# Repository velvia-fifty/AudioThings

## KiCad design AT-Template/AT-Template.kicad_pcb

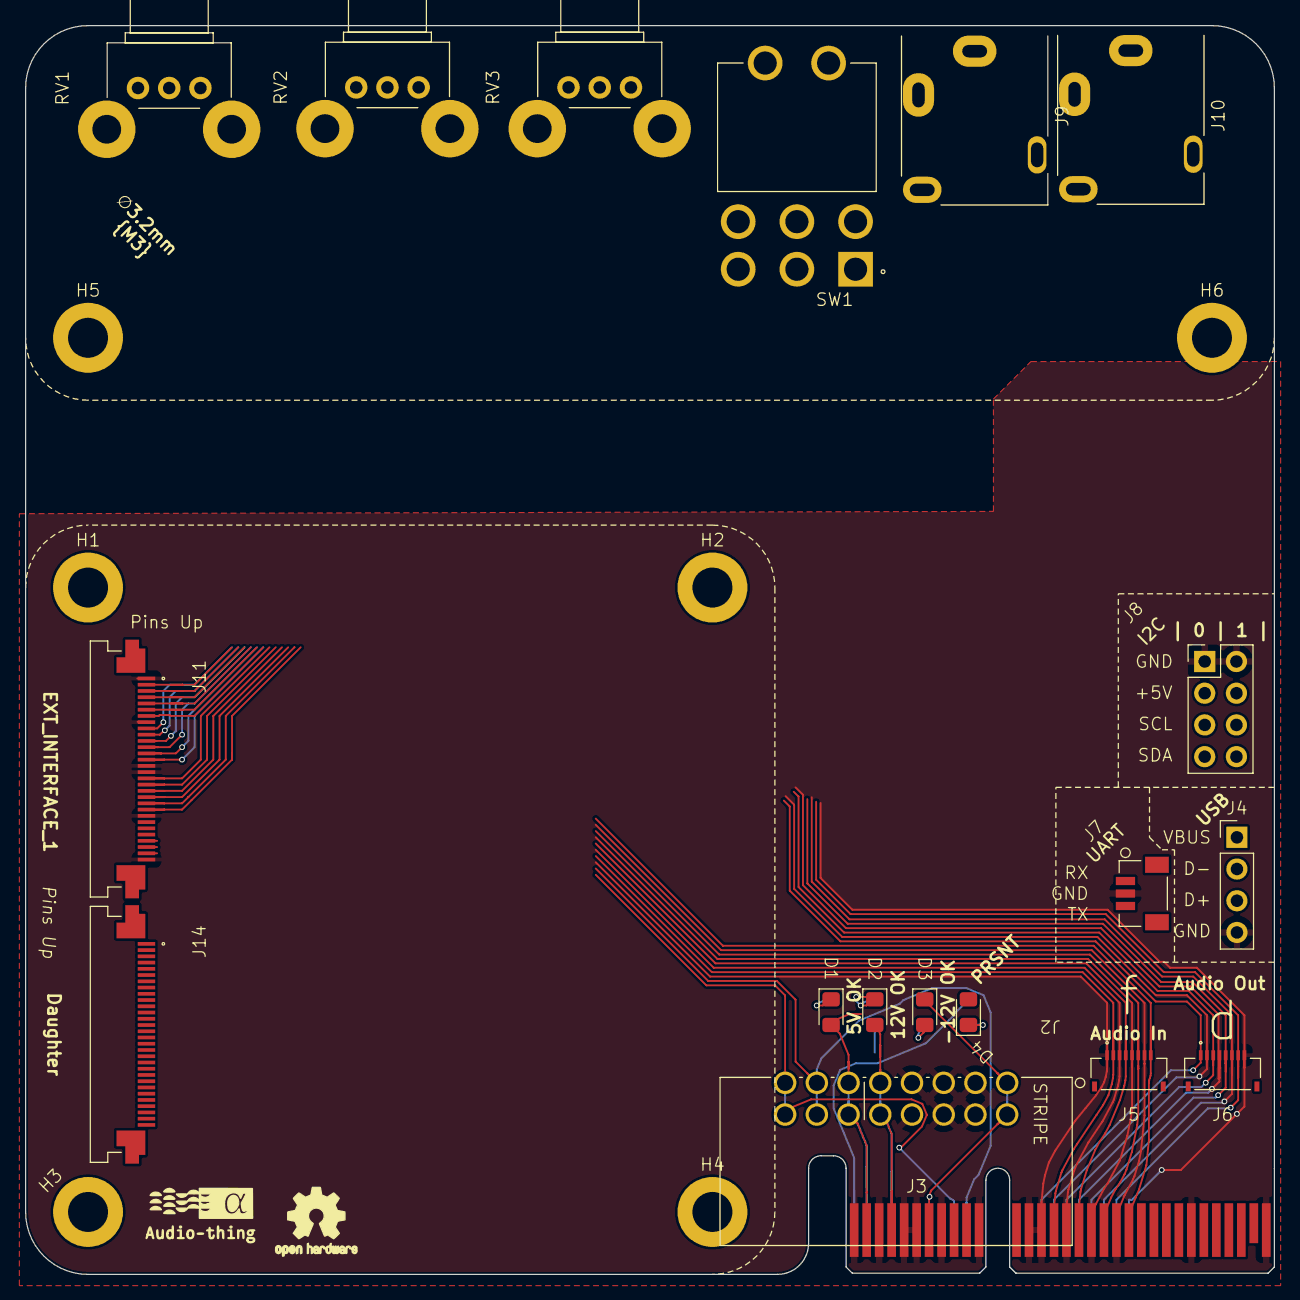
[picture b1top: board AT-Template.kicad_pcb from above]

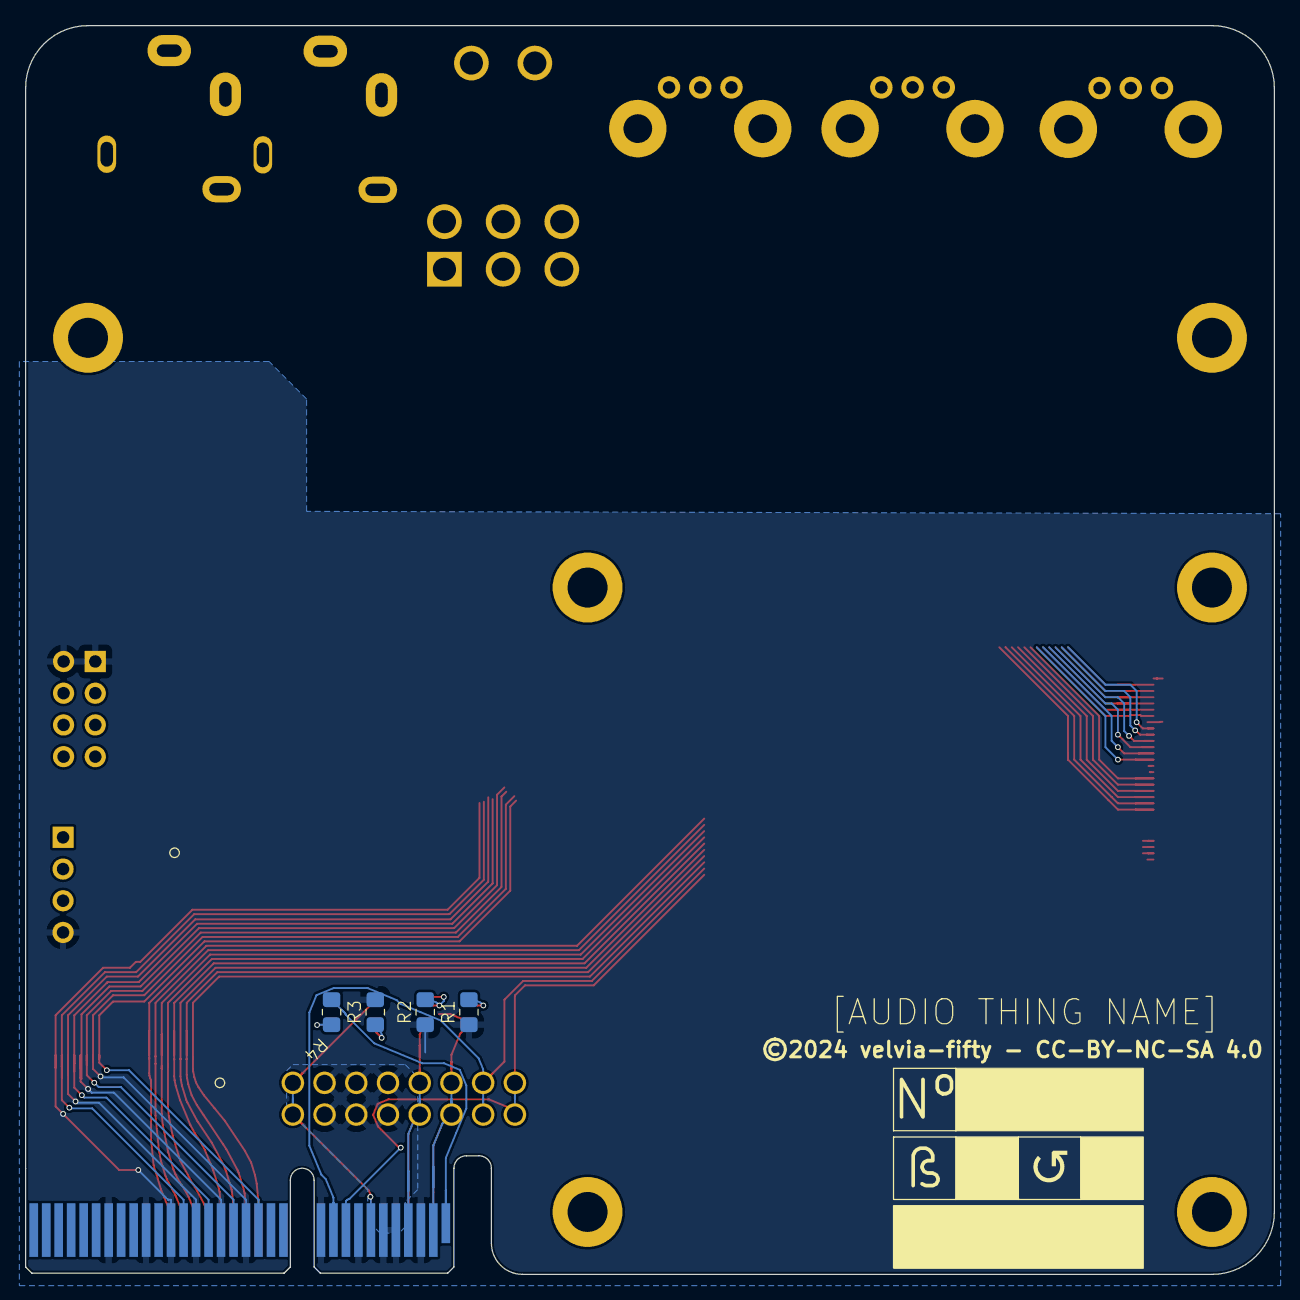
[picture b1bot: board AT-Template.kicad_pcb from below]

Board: 2 copper layers, 100.0 x 100.0 mm, 29 parts (4 on the bottom side), 29 nets.

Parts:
D1: 5V OK; LED_0805_2012Metric_Pad1.15x1.40mm_HandSolder
D2: 12V OK; LED_0805_2012Metric_Pad1.15x1.40mm_HandSolder
D3: -12V OK; LED_0805_2012Metric_Pad1.15x1.40mm_HandSolder
D4: PRSNT; LED_0805_2012Metric_Pad1.15x1.40mm_HandSolder
H1, H2, H3, H4, H5, H6: M3; MountingHole_3.2mm_M3_DIN965_Pad
J2: OPT EURO; EURORACK Right Angle
J3: BUS_PCIexpress_x4
J4: USB; PinHeader_1x04_P2.54mm_Vertical
J5: Audio In; AMPHENOL_F33B-1A7Q1-E8C08
J6: Audio Out; AMPHENOL_F33B-1A7Q1-E8C08
J7: UART; CONN_BM03B-SRSS-TBLFSN_JST
J8: I2C; PinHeader_2x04_P2.54mm_Vertical
J9, J10: Stereo Jack - THT; Jack_3.5mm_CUI_SJ1-3514N_Horizontal
J11: EXT_INTERFACE_1; AMPHENOL_SFV30R-4STE1HLF - FFC - 30 RA
J14: Daughter; AMPHENOL_SFV30R-4STE1HLF - FFC - 30 RA
R1, R4: 150; R_0805_2012Metric_Pad1.20x1.40mm_HandSolder
R2, R3: 500; R_0805_2012Metric_Pad1.20x1.40mm_HandSolder
RV1, RV2, RV3: PTV09 Pot HZ; Potentiometer_Bourns_PTV09A-2_Single_Horizontal
SW1: Micro Toggle; DPDT Micro SW_1825138-7

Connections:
+5V: D1.2 (A), J2.11, J2.12, J3.A2 (+5V), J3.B2 (+5V), J8.3, J8.4
+12V: D2.2 (A), J2.9, J2.10, J3.A4 (+12V), J3.B4 (+12V)
-12V: D3.1 (K), J2.1, J2.2, J3.A7 (-12V), J3.B7 (-12V)
/Bus/CON_CV: J2.13, J2.14, J3.A10 (EURO_CV)
/Bus/CON_GATE: J2.15, J2.16, J3.A9 (EURO_GATE)
/Bus/I2C0_SCL: J3.B23 (I2C0_SCL), J8.5
/Bus/I2C0_SDA: J3.A24 (I2C0_SDA), J8.7
/Bus/I2C1_SCL: J3.A27 (I2C1_SCL), J8.6
/Bus/I2C1_SDA: J3.B27 (I2C1_SDA), J8.8
/Bus/USB_D+: J3.B12 (USB_D+), J4.3
GND: J2.3, J2.4, J2.5, J2.6, J2.7, J2.8, J3.A3 (GND), J3.A5 (GND), J3.A6 (GND), J3.A8 (GND), J3.A11 (GND), J3.A15 (GND), J3.A17 (GND), J3.A19 (GND), J3.A21 (GND), J3.A23 (GND), J3.A26 (GND), J3.B1 (GND), J3.B3 (GND), J3.B5 (GND), J3.B6 (GND), J3.B8 (GND), J3.B11 (GND), J3.B13 (GND), J3.B14 (GND), J3.B16 (GND), J3.B18 (GND), J3.B20 (GND), J3.B26 (GND), J3.B32 (GND), J4.4, J5.1, J5.3, J5.5, J5.7, J6.2, J6.4, J6.6, J6.8, J7.2, J8.1, J8.2, J11.1, J11.8, J11.15, J11.16, J11.23, J11.30, R1.1, R2.1, R3.2
unnamed: D1.1 (K), R1.2
unnamed: D2.1 (K), R2.2
unnamed: D3.2 (A), R3.1
unnamed: D4.2 (A), J3.B31 (PRSNT_B)
unnamed: D4.1 (K), R4.2
unnamed: J3.B15 (Audio_In_A), J5.2
unnamed: J3.B17 (Audio_In_B), J5.4
unnamed: J3.B19 (Audio_In_C), J5.6
unnamed: J3.B21 (Audio_In_D), J5.8
unnamed: J3.A14 (Audio_Out_A), J6.1
unnamed: J3.A16 (Audio_Out_B), J6.3
unnamed: J3.A18 (Audio_Out_C), J6.5
unnamed: J3.A20 (Audio_Out_D), J6.7
unnamed: J3.A1 (PRSNT_A), R4.1
unnamed: J3.B22 (UART_RX), J7.1
unnamed: J3.A22 (UART_TX), J7.3
unnamed: J3.A12 (USB_5V), J4.1
unnamed: J3.A13 (USB_D-), J4.2

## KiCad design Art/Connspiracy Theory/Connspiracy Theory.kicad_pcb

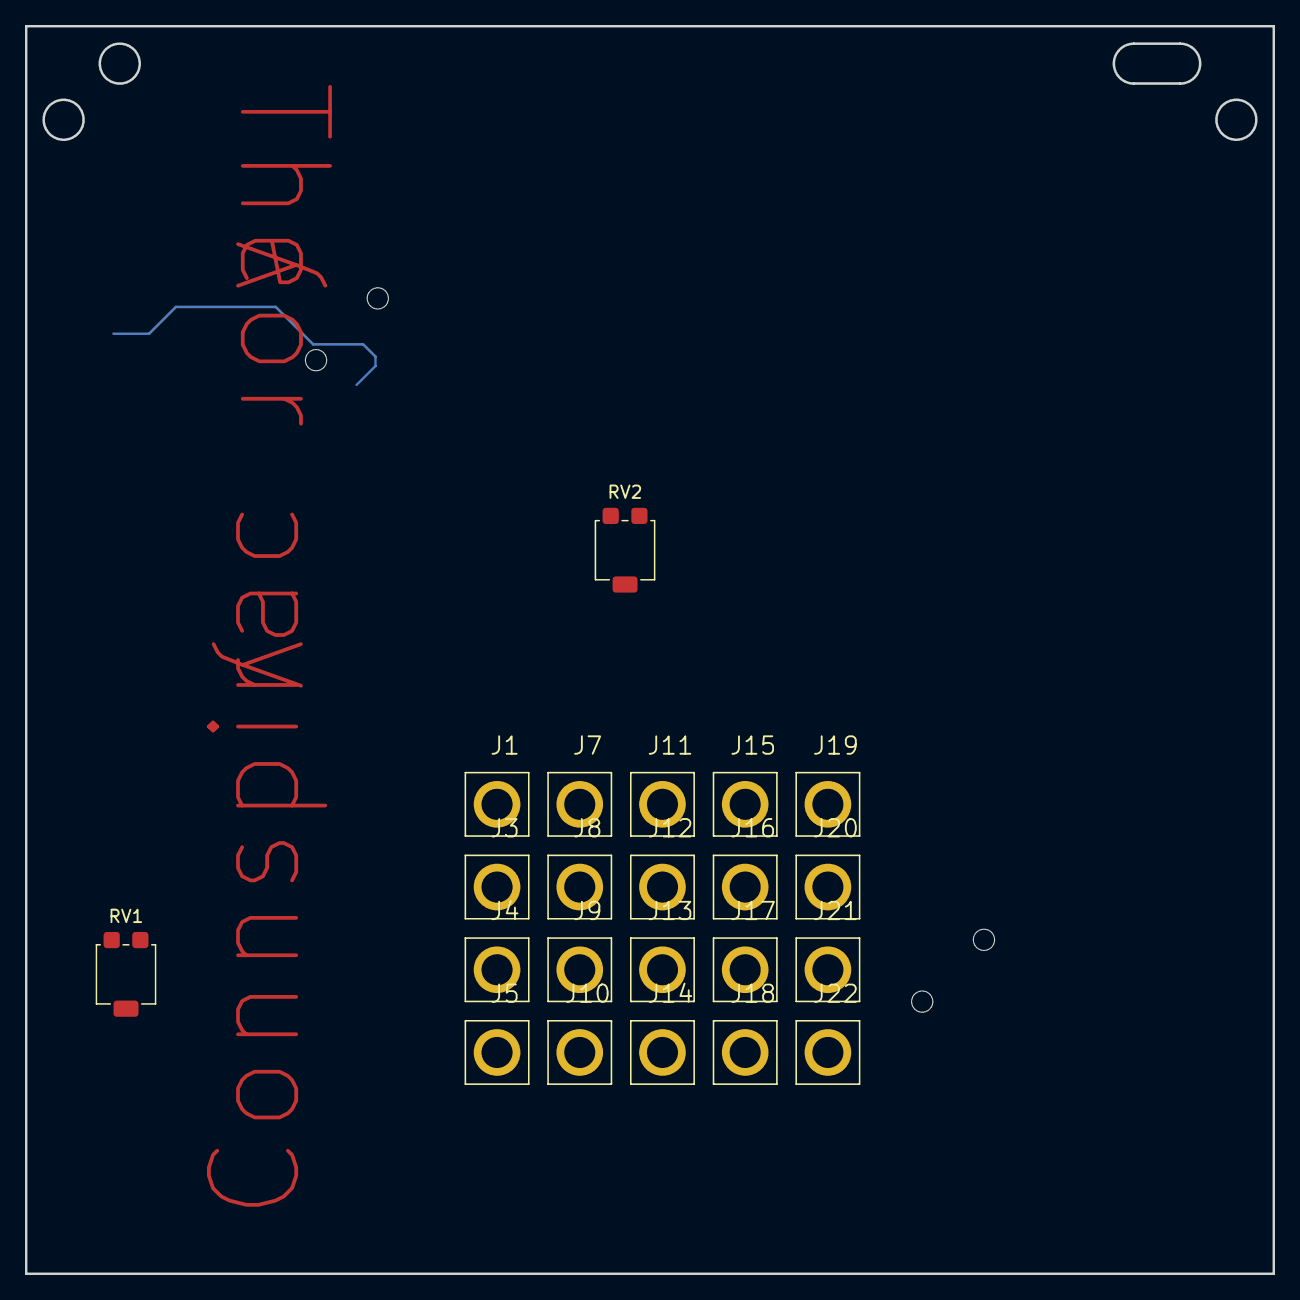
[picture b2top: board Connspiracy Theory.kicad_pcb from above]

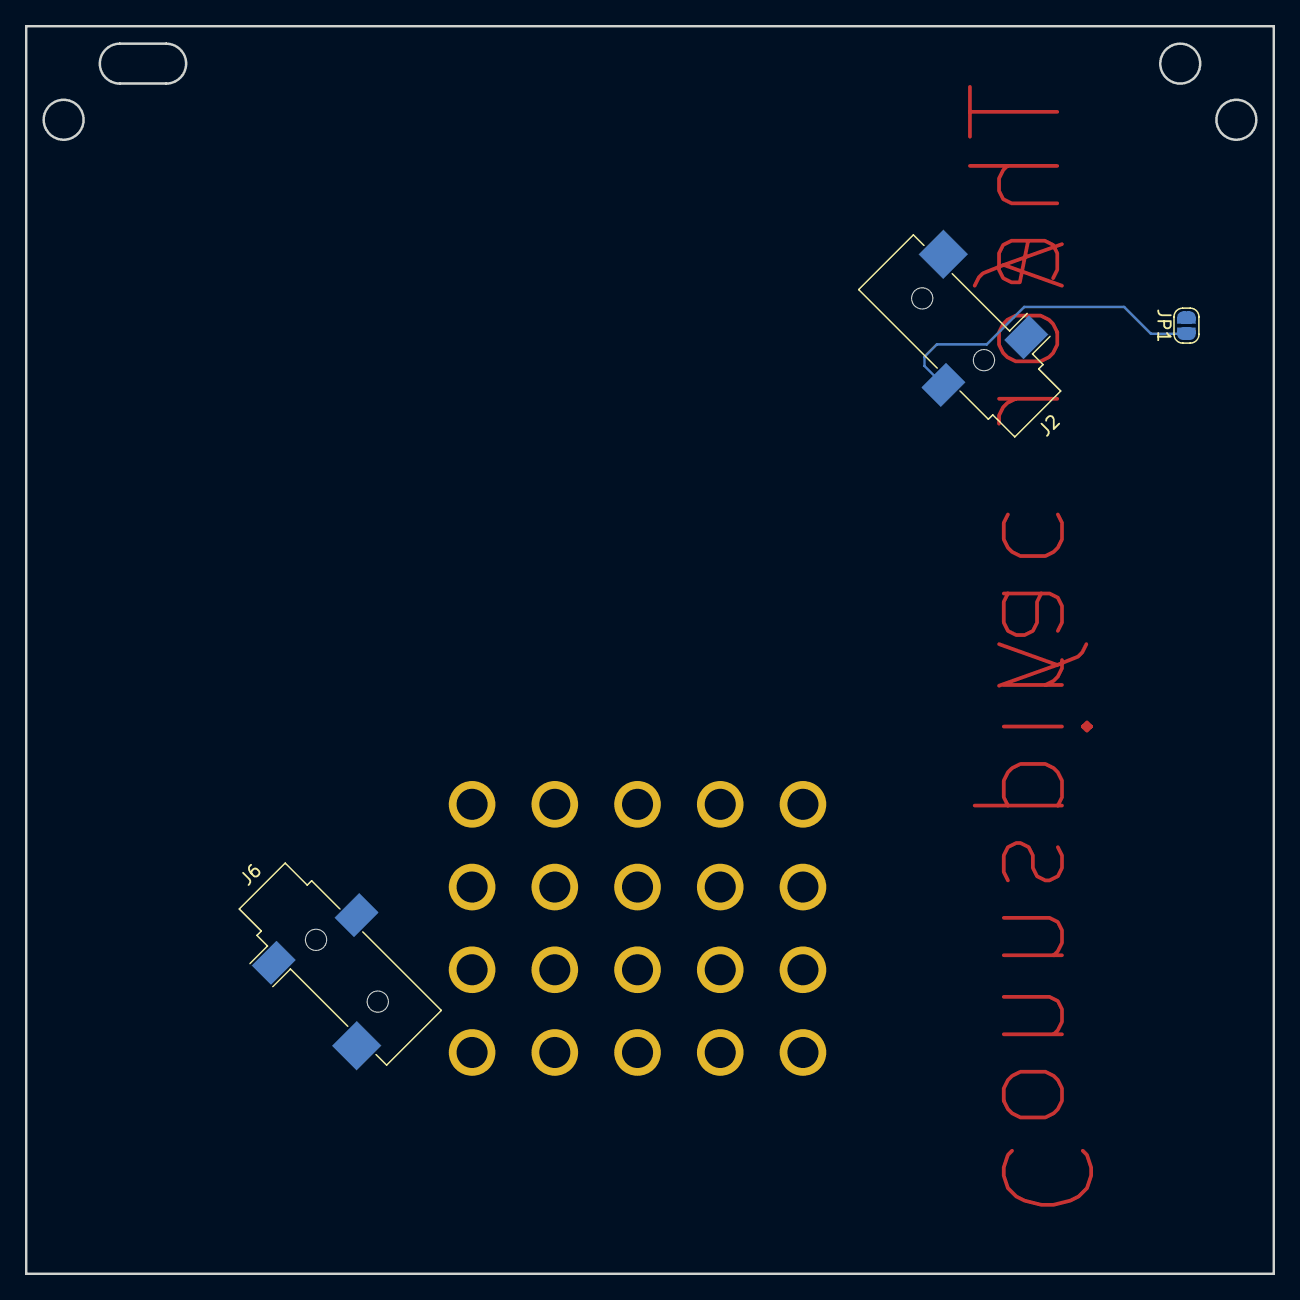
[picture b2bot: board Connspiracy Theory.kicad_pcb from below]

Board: 2 copper layers, 100.0 x 100.0 mm, 25 parts (3 on the bottom side), 12 nets.

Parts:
J1, J3, J4, J5, J7, J8, J9, J10, J11, J12, J13, J14, J15, J16, J17, J18, J19, J20, J21, J22: Turret - MILMAX_2501-2-00-80-00-00-07-0
J2: Tin; Jack_3.5mm_CUI_SJ-3523-SMT_Horizontal
J6: Foil; Jack_3.5mm_CUI_SJ-3523-SMT_Horizontal
JP1: This is a religious decision; SolderJumper-2_P1.3mm_Open_RoundedPad1.0x1.5mm
RV1: IDK like 12 Speed; Potentiometer_Bourns_3314G_Vertical
RV2: At least 12 Speed; Potentiometer_Bourns_3314G_Vertical

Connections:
/Groucho: J11.1, J12.1
/Inside: J21.1, J22.1
/Karl: J15.1, J16.1
/Outside: J13.1, J14.1
/Upsidedown: J17.1, J18.1
/Zeppo: J19.1, J20.1
GND: J2.R, JP1.1 (A), RV1.3
unnamed: J1.1, J2.T, J3.1, RV1.1
unnamed: J4.1, J5.1, RV1.2
unnamed: J6.T, J7.1, J8.1, RV2.1
unnamed: J9.1, J10.1, RV2.2
unnamed: JP1.2 (B), RV2.3

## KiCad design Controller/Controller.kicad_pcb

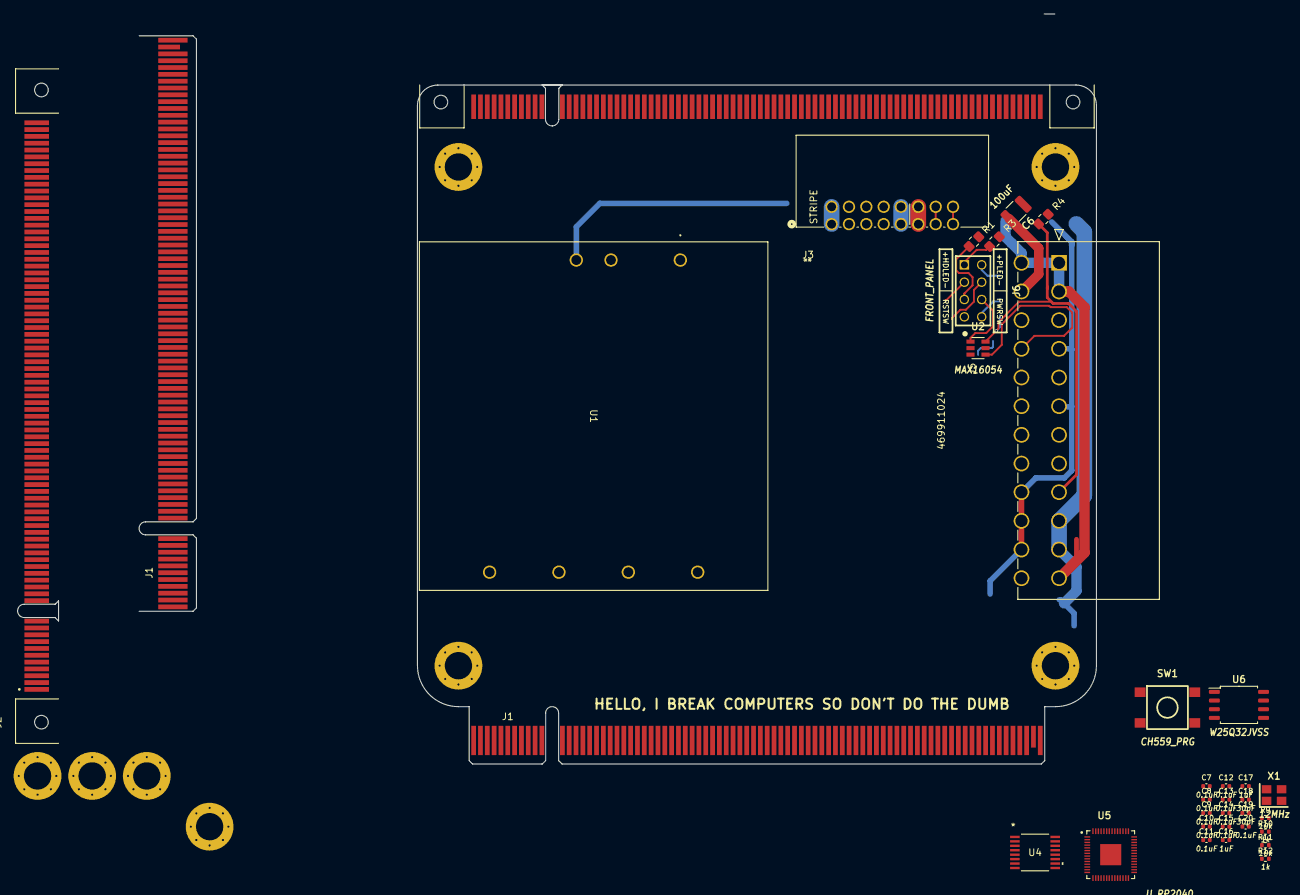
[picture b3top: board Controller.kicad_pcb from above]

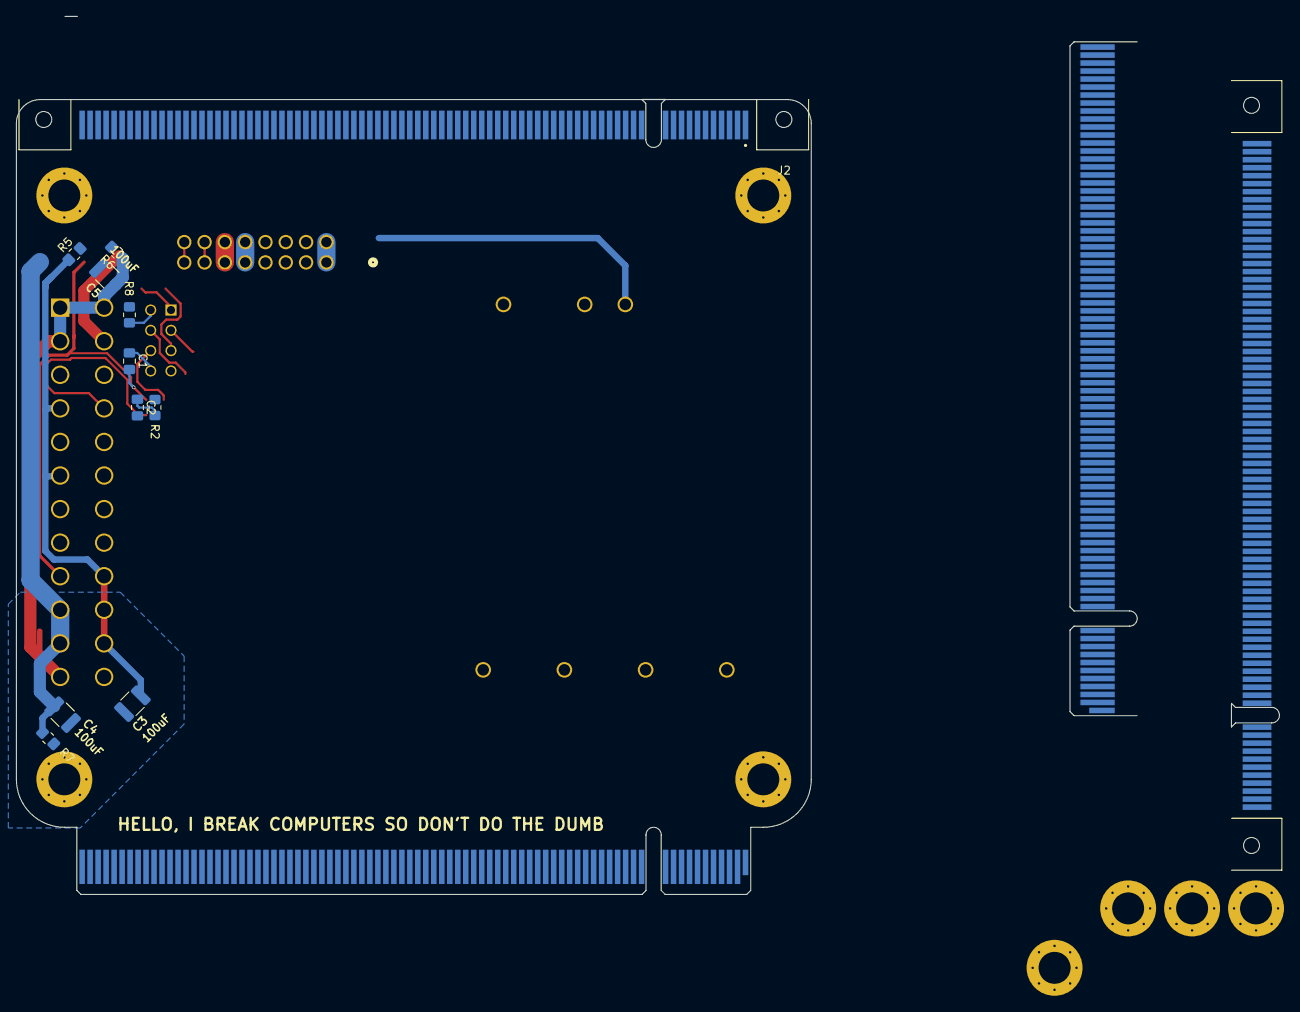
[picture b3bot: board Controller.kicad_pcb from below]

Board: 2 copper layers, 54 parts (11 on the bottom side), 34 nets.

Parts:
C1: 0.1uF; C_0805_2012Metric_Pad1.18x1.45mm_HandSolder
C2: 10uF; C_0805_2012Metric_Pad1.18x1.45mm_HandSolder
C3, C4, C5, C6: 100uF; C_1210_3225Metric
C7, C8, C9, C10, C11, C12, C13, C14, C15, C20: 0.1uF; C_0402_1005Metric
C16, C17: 1uF; C_0402_1005Metric
C18, C19: 30pF; C_0402_1005Metric
H1, H5, H5#2, H6, H6#2, H7, H7#2, H8: H_HOLE; H_ATX_PERF
J1: EURO_EXPRESS; BUS_EUROexpress
J1#2: Bus_EURO_Express; BUS_PCIexpress_x16
J2, J2#2: 10025026-10103TLF; AMPHENOL_10025026-10103TLF
J3: EURO_CONN; EURORACK Right Angle
J5: ATX_POWER; ATX_24_RIGHT_ANGLE_MOLEX_469911024
J6: FRONT_PANEL; P_CONN_PANEL
R1: 10k; R_0805_2012Metric_Pad1.20x1.40mm_HandSolder
R2, R4, R5, R6, R7: 470; R_0805_2012Metric_Pad1.20x1.40mm_HandSolder
R3, R8: 330; R_0805_2012Metric_Pad1.20x1.40mm_HandSolder
R9, R11: 10k; R_0402_1005Metric
R10, R12: 1k; R_0402_1005Metric
SW1: CH559_PRG; SW_B3FS-1010
U1: DKA30A-12; DKA30_MWU
U2: MAX16054; U_TSOT-23-6
U4: TMUX4051PWR; TSSOP16_PW_TEX
U5: U_RP2040; U_QFN40P700X700X90-57N
U6: W25Q32JVSS; U_SOIC-8_5.23x5.23mm_P1.27mm
X1: 12MHz; X_SMD3225

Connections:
+3.3V: C5.1, J5.1 (+3.3V), J5.2 (+3.3V), J5.12 (+3.3V), J5.13 (+3.3V), R6.1
+5V: J1.A8 (+5v), J1.B9 (+5v), J1.B10 (+5v), J3.11, J3.12
+5VSB: C1.2, J5.9 (+5VSB), R4.1, U2.6 (VCC)
+12V: C4.1, J1.A5 (-12v), J1.A6 (-12v), J1.A7 (-12v), J1.B5 (-12v), J1.B6 (-12v), J3.9, J3.10, J5.10 (+12V), J5.11 (+12V), R7.1, U1.4 (+VIN)
+12VA: U1.5 (+VOUT), U4.16 (VDD)
-12V: C6.2, J1.A2 (+12v), J1.A3 (+12v), J1.B1 (+12v), J1.B2 (+12v), J1.B3 (+12v), J3.1, J3.2, J5.14 (-12V)
-12VA: U1.7 (-VOUT), U4.7 (VSS)
/BOOTSEL: R12.2, SW1.1 (A)
/CV: J1.A14 (CV_IN), J3.13, J3.14
/GATE: J1.A17 (GATE_IN), J3.15, J3.16
/HDD_LED+: J6.1, R3.2
/PWR_LED+: J6.8, R8.2
/QSPI_CS: R11.1, R12.1, U5.56 (QSPI_CSN), U6.1 (~CS)
/QSPI_SCK: U5.52 (QSPI_SCLK), U6.6 (CLK)
/QSPI_SD0: U5.53 (QSPI_SD0), U6.5 (DI(IO0))
/QSPI_SD1: U5.55 (QSPI_SD1), U6.2 (DO(IO1))
/QSPI_SD2: U5.54 (QSPI_SD2), U6.3 (IO2)
/QSPI_SD3: U5.51 (QSPI_SD3), U6.7 (IO3)
/~PS_ON: J5.16 (~PS_ON), U2.4 (~OUT)
/~PWR_SW: J6.6, U2.1 (IN)
/~RST_SIG: C2.1, R2.1
/~RST_SW: J6.3, R1.2, R2.2
GND: C1.1, C2.2, C3.2, C4.2, C5.2, C6.1, C7.1, C8.1, C9.1, C10.1, C11.1, C12.1, C13.1, C14.1, C15.1, C16.2, C17.2, C18.2, C19.2, C20.1, H1.1, H5.1, H5#2.1, H6.1, H6#2.1, H7.1, H8.1, J1.A4 (GND), J1.A11 (GND), J1.A12 (GND), J1.A15 (GND), J1.B4 (GND), J1.B7 (GND), J1.B13 (GND), J1.B16 (GND), J1.B18 (GND), J3.3, J3.4, J3.5, J3.6, J3.7, J3.8, J5.3 (GND), J5.5 (GND), J5.7 (GND), J5.15 (GND), J5.17 (GND), J5.18 (GND), J5.19 (GND), J5.24 (GND), J6.4, J6.5, R4.2, R5.2, R6.2, R7.2, SW1.2 (B), U1.3 (-VIN), U2.2 (GND), U2.3 (CLEAR), U5.19 (TESTEN), U5.57 (GND), U6.4 (GND), X1.2, X1.4
GNDA: U1.6 (COM), U4.8 (GND)
unnamed: C18.1, R10.2, X1.3
unnamed: J1#2.A9 (+3.3V), J1#2.A10 (+3.3V), J1#2.B8 (+3.3V)
unnamed: J1#2.A2 (+12V), J1#2.A3 (+12V), J1#2.B1 (+12V), J1#2.B2 (+12V), J1#2.B3 (+12V)
unnamed: J1#2.A4 (GND), J1#2.A12 (GND), J1#2.A15 (GND), J1#2.A18 (GND), J1#2.A20 (GND), J1#2.A23 (GND), J1#2.A24 (GND), J1#2.A27 (GND), J1#2.A28 (GND), J1#2.A31 (GND), J1#2.A34 (GND), J1#2.A37 (GND), J1#2.A38 (GND), J1#2.A41 (GND), J1#2.A42 (GND), J1#2.A45 (GND), J1#2.A46 (GND), J1#2.A49 (GND), J1#2.A51 (GND), J1#2.A54 (GND), J1#2.A55 (GND), J1#2.A58 (GND), J1#2.A59 (GND), J1#2.A62 (GND), J1#2.A63 (GND), J1#2.A66 (GND), J1#2.A67 (GND), J1#2.A70 (GND), J1#2.A71 (GND), J1#2.A74 (GND), J1#2.A75 (GND), J1#2.A78 (GND), J1#2.A79 (GND), J1#2.A82 (GND), J1#2.B4 (GND), J1#2.B7 (GND), J1#2.B13 (GND), J1#2.B16 (GND), J1#2.B18 (GND), J1#2.B21 (GND), J1#2.B22 (GND), J1#2.B25 (GND), J1#2.B26 (GND), J1#2.B29 (GND), J1#2.B32 (GND), J1#2.B35 (GND), J1#2.B36 (GND), J1#2.B39 (GND), J1#2.B40 (GND), J1#2.B43 (GND), J1#2.B44 (GND), J1#2.B47 (GND), J1#2.B49 (GND), J1#2.B52 (GND), J1#2.B53 (GND), J1#2.B56 (GND), J1#2.B57 (GND), J1#2.B60 (GND), J1#2.B61 (GND), J1#2.B64 (GND), J1#2.B65 (GND), J1#2.B68 (GND), J1#2.B69 (GND), J1#2.B72 (GND), J1#2.B73 (GND), J1#2.B76 (GND), J1#2.B77 (GND), J1#2.B80 (GND)
unnamed: R9.2, U5.26 (RUN)
unnamed: C19.1, U5.20 (XIN), X1.1
unnamed: R10.1, U5.21 (XOUT)
RP_1.1V: C14.2, C15.2, C17.1, U5.23 (DVDD), U5.45 (VREG_VOUT), U5.50 (DVDD)
RP_3.3V: C7.2, C8.2, C9.2, C10.2, C11.2, C12.2, C13.2, C16.1, C20.2, R11.2, U5.1 (IOVDD), U5.10 (IOVDD), U5.22 (IOVDD), U5.33 (IOVDD), U5.42 (IOVDD), U5.43 (ADC_AVDD), U5.44 (VREG_VIN), U5.48 (USB_VDD), U5.49 (IOVDD), U6.8 (VCC)
VCC: C3.1, J5.4 (+5V), J5.6 (+5V), J5.21 (+5V), J5.22 (+5V), J5.23 (+5V), R1.1, R3.1, R5.1, R8.1

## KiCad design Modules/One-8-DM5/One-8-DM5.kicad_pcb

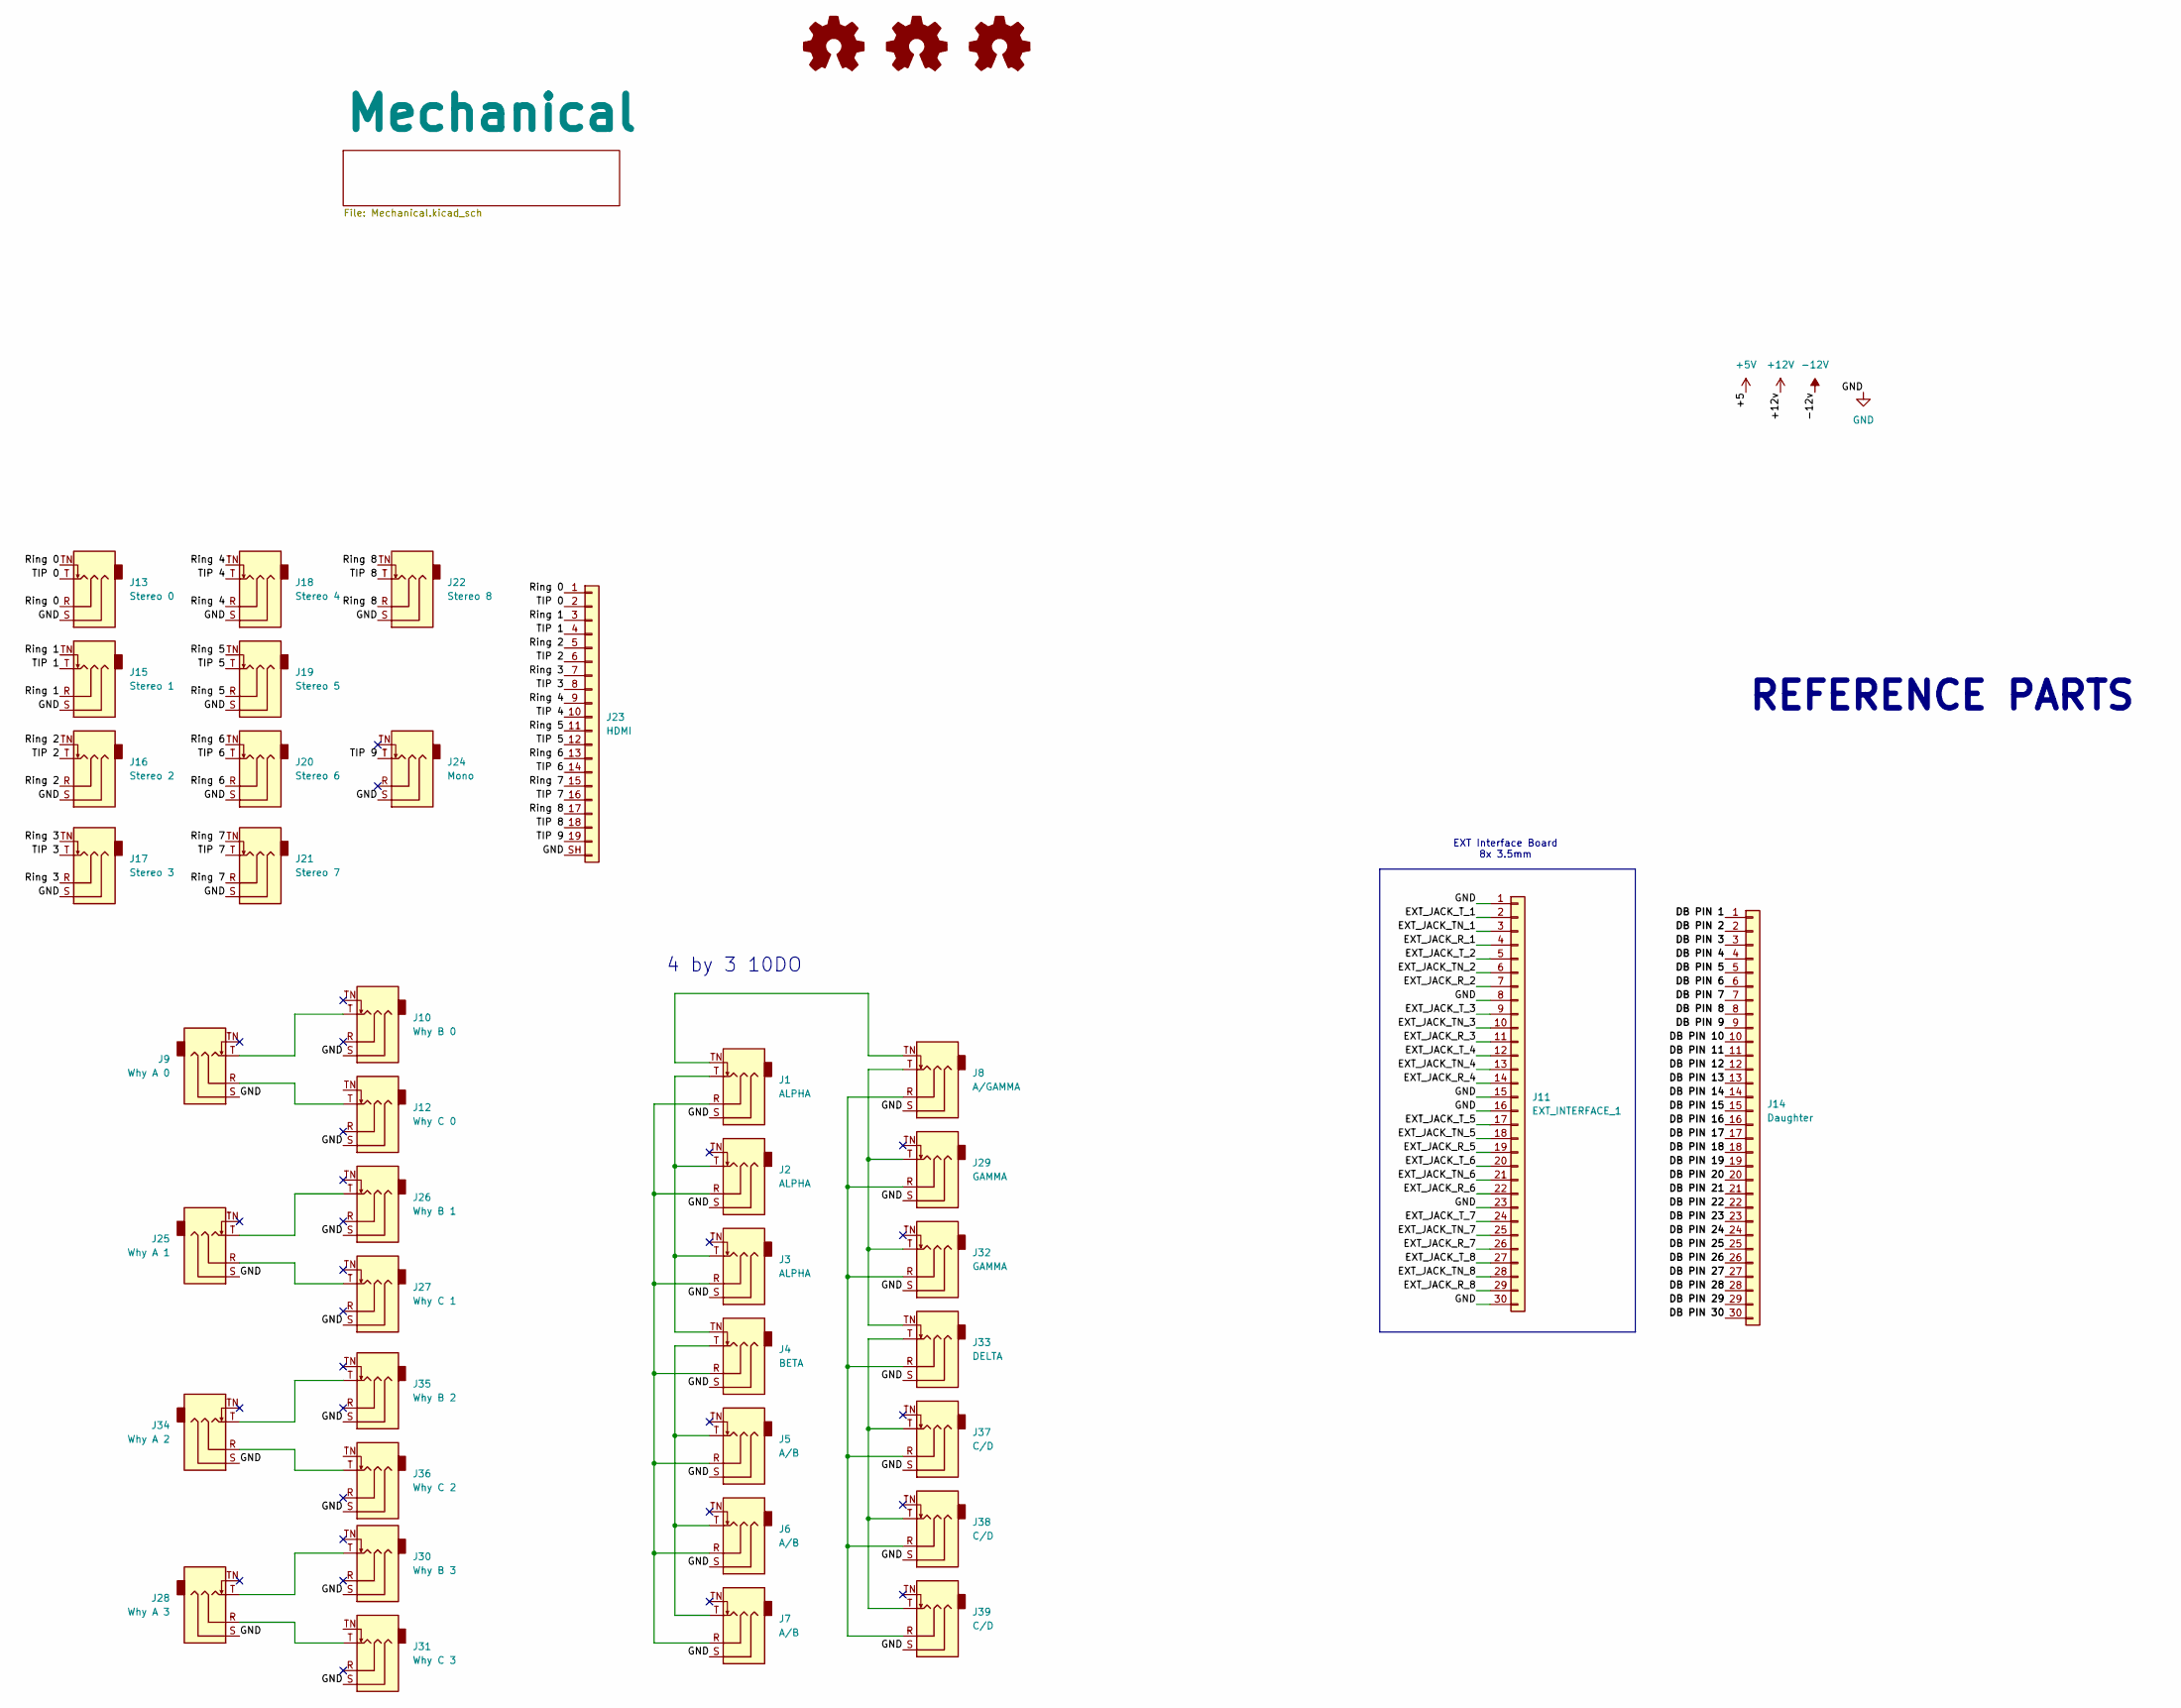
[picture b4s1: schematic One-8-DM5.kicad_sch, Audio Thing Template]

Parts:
J1, J2, J3: ALPHA; Jack_3.5mm_CUI_SJ-3524-SMT_Horizontal
J4: BETA; Jack_3.5mm_CUI_SJ-3524-SMT_Horizontal
J5, J6, J7: A/B; Jack_3.5mm_CUI_SJ-3524-SMT_Horizontal
J8: A/GAMMA; Jack_3.5mm_CUI_SJ-3524-SMT_Horizontal
J9: Why A 0; Jack_3.5mm_CUI_SJ-3524-SMT_Horizontal
J10: Why B 0; Jack_3.5mm_CUI_SJ-3524-SMT_Horizontal
J11: EXT_INTERFACE_1; AMPHENOL_SFV30R-4STE1HLF - FFC - 30 RA
J12: Why C 0; Jack_3.5mm_CUI_SJ-3524-SMT_Horizontal
J13: Stereo 0; Jack_3.5mm_CUI_SJ-3524-SMT_Horizontal
J14: Daughter; AMPHENOL_SFV30R-4STE1HLF - FFC - 30 RA
J15: Stereo 1; Jack_3.5mm_CUI_SJ-3524-SMT_Horizontal
J16: Stereo 2; Jack_3.5mm_CUI_SJ-3524-SMT_Horizontal
J17: Stereo 3; Jack_3.5mm_CUI_SJ-3524-SMT_Horizontal
J18: Stereo 4; Jack_3.5mm_CUI_SJ-3524-SMT_Horizontal
J19: Stereo 5; Jack_3.5mm_CUI_SJ-3524-SMT_Horizontal
J20: Stereo 6; Jack_3.5mm_CUI_SJ-3524-SMT_Horizontal
J21: Stereo 7; Jack_3.5mm_CUI_SJ-3524-SMT_Horizontal
J22: Stereo 8; Jack_3.5mm_CUI_SJ-3524-SMT_Horizontal
J23: HDMI; HDMI_A_Molex_208658-1001_Horizontal
J24: Mono; Jack_3.5mm_CUI_SJ-3524-SMT_Horizontal
J25: Why A 1; Jack_3.5mm_CUI_SJ-3524-SMT_Horizontal
J26: Why B 1; Jack_3.5mm_CUI_SJ-3524-SMT_Horizontal
J27: Why C 1; Jack_3.5mm_CUI_SJ-3524-SMT_Horizontal
J28: Why A 3; Jack_3.5mm_CUI_SJ-3524-SMT_Horizontal
J29, J32: GAMMA; Jack_3.5mm_CUI_SJ-3524-SMT_Horizontal
J30: Why B 3; Jack_3.5mm_CUI_SJ-3524-SMT_Horizontal
J31: Why C 3; Jack_3.5mm_CUI_SJ-3524-SMT_Horizontal
J33: DELTA; Jack_3.5mm_CUI_SJ-3524-SMT_Horizontal
J34: Why A 2; Jack_3.5mm_CUI_SJ-3524-SMT_Horizontal
J35: Why B 2; Jack_3.5mm_CUI_SJ-3524-SMT_Horizontal
J36: Why C 2; Jack_3.5mm_CUI_SJ-3524-SMT_Horizontal
J37, J38, J39: C/D; Jack_3.5mm_CUI_SJ-3524-SMT_Horizontal

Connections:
/DB PIN 1: J14.1
/DB PIN 2: J14.2
/DB PIN 3: J14.3
/DB PIN 4: J14.4
/DB PIN 5: J14.5
/DB PIN 6: J14.6
/DB PIN 7: J14.7
/DB PIN 8: J14.8
/DB PIN 9: J14.9
/DB PIN 10: J14.10
/DB PIN 11: J14.11
/DB PIN 12: J14.12
/DB PIN 13: J14.13
/DB PIN 14: J14.14
/DB PIN 15: J14.15
/DB PIN 16: J14.16
/DB PIN 17: J14.17
/DB PIN 18: J14.18
/DB PIN 19: J14.19
/DB PIN 20: J14.20
/DB PIN 21: J14.21
/DB PIN 22: J14.22
/DB PIN 23: J14.23
/DB PIN 24: J14.24
/DB PIN 25: J14.25
/DB PIN 26: J14.26
/DB PIN 27: J14.27
/DB PIN 28: J14.28
/DB PIN 29: J14.29
/DB PIN 30: J14.30
/EXT_JACK_R_1: J11.4
/EXT_JACK_R_2: J11.7
/EXT_JACK_R_3: J11.11
/EXT_JACK_R_4: J11.14
/EXT_JACK_R_5: J11.19
/EXT_JACK_R_6: J11.22
/EXT_JACK_R_7: J11.26
/EXT_JACK_R_8: J11.29
/EXT_JACK_TN_1: J11.3
/EXT_JACK_TN_2: J11.6
/EXT_JACK_TN_3: J11.10
/EXT_JACK_TN_4: J11.13
/EXT_JACK_TN_5: J11.18
/EXT_JACK_TN_6: J11.21
/EXT_JACK_TN_7: J11.25
/EXT_JACK_TN_8: J11.28
/EXT_JACK_T_1: J11.2
/EXT_JACK_T_2: J11.5
/EXT_JACK_T_3: J11.9
/EXT_JACK_T_4: J11.12
/EXT_JACK_T_5: J11.17
/EXT_JACK_T_6: J11.20
/EXT_JACK_T_7: J11.24
/EXT_JACK_T_8: J11.27
/Ring 0: J13.R, J13.TN, J23.1
/Ring 1: J15.R, J15.TN, J23.3
/Ring 2: J16.R, J16.TN, J23.5
/Ring 3: J17.R, J17.TN, J23.7
/Ring 4: J18.R, J18.TN, J23.9
/Ring 5: J19.R, J19.TN, J23.11
/Ring 6: J20.R, J20.TN, J23.13
/Ring 7: J21.R, J21.TN, J23.15
/Ring 8: J22.R, J22.TN, J23.17
/TIP 0: J13.T, J23.2
/TIP 1: J15.T, J23.4
/TIP 2: J16.T, J23.6
/TIP 3: J17.T, J23.8
/TIP 4: J18.T, J23.10
/TIP 5: J19.T, J23.12
/TIP 6: J20.T, J23.14
/TIP 7: J21.T, J23.16
/TIP 8: J22.T, J23.18
/TIP 9: J23.19, J24.T
GND: J1.S, J2.S, J3.S, J4.S, J5.S, J6.S, J7.S, J8.S, J9.S, J10.S, J11.1, J11.8, J11.15, J11.16, J11.23, J11.30, J12.S, J13.S, J15.S, J16.S, J17.S, J18.S, J19.S, J20.S, J21.S, J22.S, J23.SH (Sheild), J24.S, J25.S, J26.S, J27.S, J28.S, J29.S, J30.S, J31.S, J32.S, J33.S, J34.S, J35.S, J36.S, J37.S, J38.S, J39.S
unnamed: J1.R, J2.R, J3.R, J4.R, J5.R, J6.R, J7.R
unnamed: J1.T, J2.T, J3.T, J4.TN
unnamed: J1.TN, J8.TN
unnamed: J4.T, J5.T, J6.T, J7.T
unnamed: J9.T, J10.T
unnamed: J9.R, J12.T
unnamed: J25.R, J27.T
unnamed: J25.T, J26.T
unnamed: J28.R, J31.T
unnamed: J28.T, J30.T
unnamed: J8.R, J29.R, J32.R, J33.R, J37.R, J38.R, J39.R
unnamed: J8.T, J29.T, J32.T, J33.TN
unnamed: J33.T, J37.T, J38.T, J39.T
unnamed: J34.R, J36.T
unnamed: J34.T, J35.T

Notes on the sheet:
4 by 3 10DO
REFERENCE PARTS
EXT Interface Board 8x 3.5mm

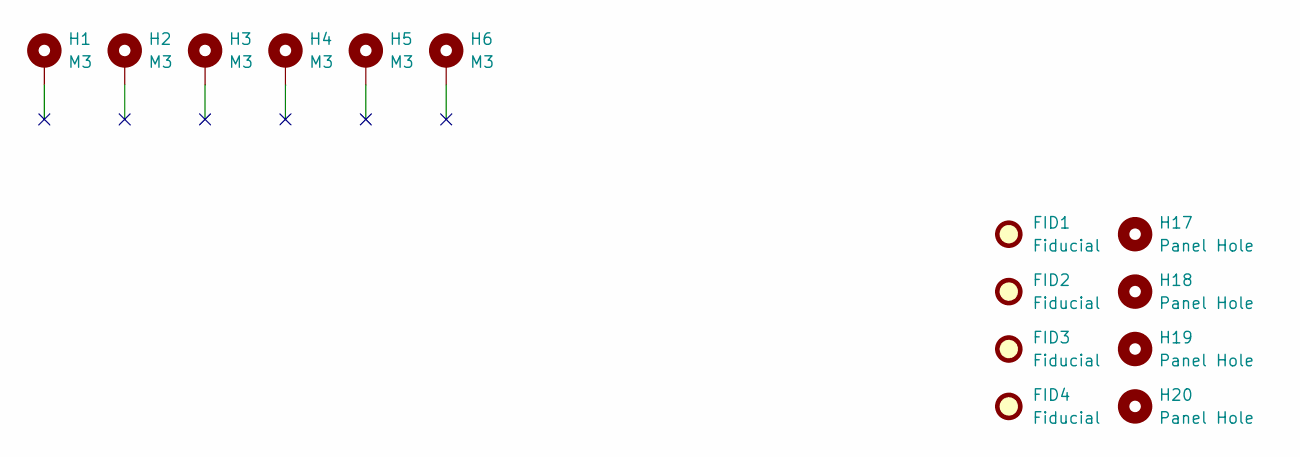
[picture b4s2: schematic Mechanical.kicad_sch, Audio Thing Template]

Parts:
FID1, FID2, FID3, FID4: Fiducial; Fiducial_1mm_Mask3mm
H1, H2, H3, H4, H5, H6: M3; MountingHole_3.2mm_M3_DIN965_Pad
H17, H18, H19, H20: Panel Hole; Panel - Hole

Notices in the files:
AT-Template/AT-Template.kicad_pcb:
©2024 velvia-fifty - CC-BY-NC-SA 4.0
